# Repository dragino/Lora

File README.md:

Hardware and software source for Lora technology

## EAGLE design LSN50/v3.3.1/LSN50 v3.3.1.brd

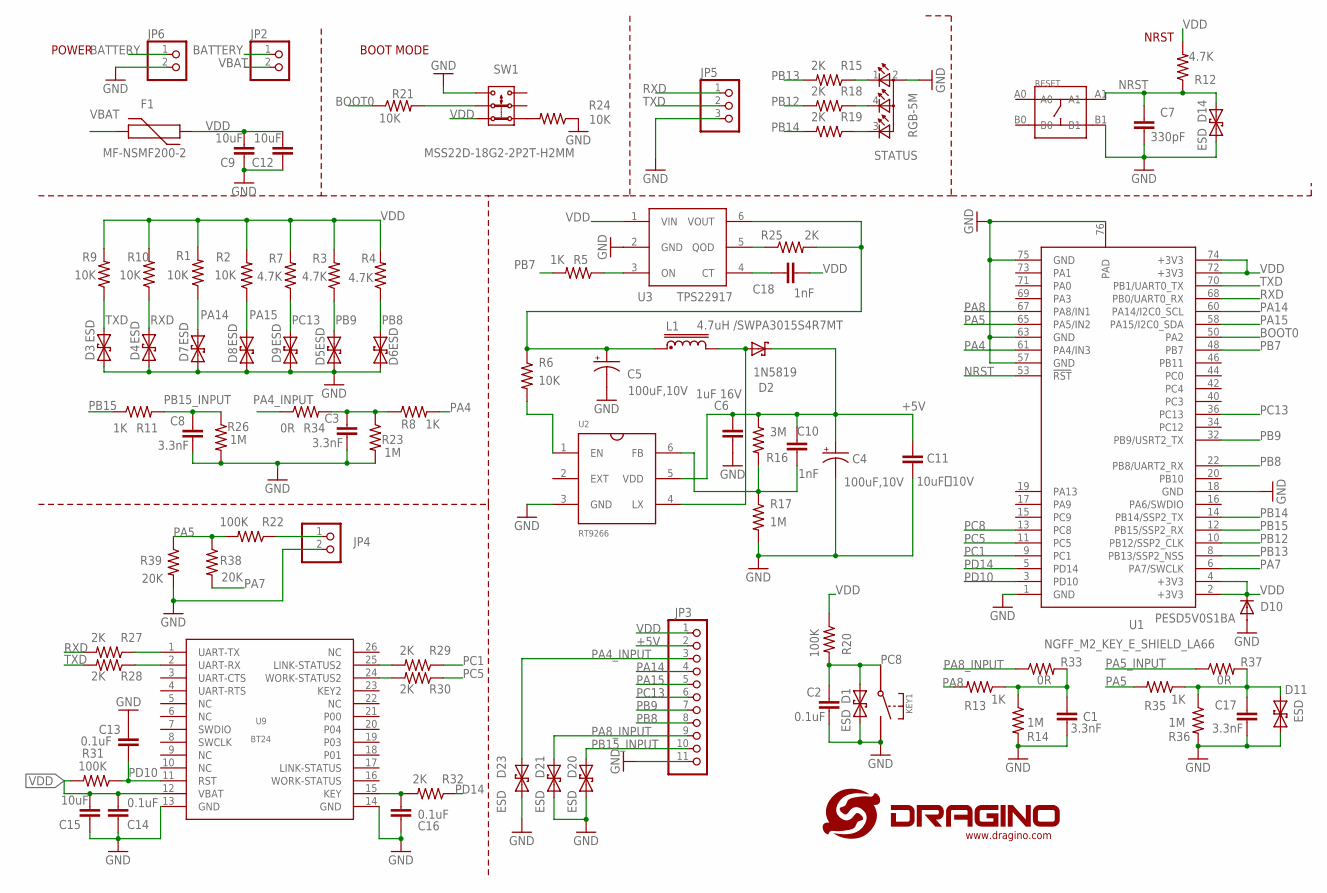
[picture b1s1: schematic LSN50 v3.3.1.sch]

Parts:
C1, C3, C8, C17: 3.3nF; C0402
C2, C13, C14, C16: 0.1uF; C0402
C4, C5: 100uF,10V; SMC_B
C6: 1uF 16V; C0603
C7: 330pF; C0402
C9, C12, C15: 10uF; C0805
C10, C18: 1nF; C0402
C11: 10uF，10V; C0805
D1, D3, D4, D5, D6, D7, D8, D9, D11, D14, D20, D21, D23: ESD; DFN1006
D2: 1N5819; SOD123FL
D10: PESD5V0S1BA; DIODE_SOD323-R
F1: MF-NSMF200-2; R1206
JP2: PINHD-1X2; 1X02
JP3: PINHD-1X11-MM; KF350-11P
JP4: PINHD-1X2-; PH2.0-2P
JP5: PINHD-1X3; 1X03
JP6: PINHD-1X2""; XH2.54-2P
KEY1: SWITCHDIL4; SWITCH_6X6X19_DIL4
L1: 4.7uH /SWPA3015S4R7MT; SWPA3010S
R1, R2, R6, R9, R10, R21, R24: 10K; R0402
R3, R4, R7, R12: 4.7K; R0402
R5, R8, R11, R13, R35: 1K; R0402
R14, R17, R23, R26, R36: 1M; R0603
R15, R18, R19, R25, R27, R28, R29, R30, R32: 2K; R0402
R16: 3M; R0402
R20, R22, R31: 100K; R0402
R33, R34, R37: 0R; R0603
R38, R39: 20K; R0402
RESET: 轻触开关3*3*1.5四脚贴片开关; SW4-SMD-3.35X3.35X1.5MM
STATUS: RGB-5M; RGB
SW1: MSS22D-18G2-2P2T-H2MM; MSS22D-18G2-2P2T-H2MM-DIL
U1: NGFF_M2_KEY_E_SHIELD_LA66; NGFF_M2_KEY_E_SHIELD
U2: RT9266; 6/SOT-23
U3: TPS22917; SOT23-6L
U9: BT24; BT24-SMD26

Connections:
+5V: C4.+, C6.2, C10.2, C11.2, D2.C, JP3.2, R16.1, U2.5 (VDD)
BATTERY: JP2.1, JP6.1
BOOT0: R21.1, U1.50 (PA2)
GND: C1.1, C2.1, C3.1, C4.-, C5.-, C6.1, C7.1, C8.1, C9.1, C11.1, C12.1, C13.2, C14.2, C15.1, C16.2, C17.1, D1.1, D3.1, D4.1, D5.1, D6.1, D7.1, D8.1, D9.1, D10.A, D11.1, D14.1, D20.1, D21.1, D23.1, JP3.11, JP4.2, JP5.3, JP6.2, KEY1.2, R14.2, R17.2, R23.2, R24.1, R26.2, R36.2, R39.2, RESET.B1, STATUS.2 (A), SW1.1, U1.1 (GND), U1.18 (GND), U1.57 (GND), U1.63 (GND), U1.75 (GND), U1.76 (PAD), U2.3 (GND), U3.2 (GND), U9.13 (GND), U9.14 (GND)
unnamed: R15.1, STATUS.1 (CRED)
unnamed: R24.2, SW1.4
unnamed: R5.1, U3.3 (ON)
unnamed: C10.1, R16.2, R17.1, U2.6 (FB)
unnamed: D2.A, L1.P$2 (4), U2.4 (LX)
unnamed: R18.1, STATUS.4 (CBLUE)
unnamed: R6.2, U2.1 (EN)
unnamed: R25.1, U3.5 (QOD)
unnamed: R19.1, STATUS.3 (CGREEN)
unnamed: C1.2, R13.1, R14.1, R33.2
unnamed: C5.+, L1.P$1 (1), R6.1, R25.2, U3.6 (VOUT)
unnamed: R27.1, U9.1 (UART-TX)
unnamed: R28.1, U9.2 (UART-RX)
unnamed: C16.1, R32.2, U9.15 (KEY)
unnamed: C3.2, R8.1, R23.1, R34.2
unnamed: R29.2, U9.25 (LINK-STATUS2)
unnamed: R30.2, U9.24 (WORK-STATUS2)
unnamed: C17.2, D11.2, R35.1, R36.1, R37.2
unnamed: R21.2, SW1.2
unnamed: C18.1, U3.4 (CT)
unnamed: JP4.1, R22.1
NRST: C7.2, D14.2, R12.1, RESET.A1, U1.53 (!RST)
PA4: R8.2, U1.61 (PA4/IN3)
PA4_INPUT: D23.2, JP3.3, R34.1
PA5: R22.2, R35.2, R38.1, R39.1, U1.65 (PA5/IN2)
PA5_INPUT: R37.1
PA7: R38.2, U1.6 (PA7/SWCLK)
PA8: R13.2, U1.67 (PA8/IN1)
PA8_INPUT: D21.2, JP3.9, R33.1
PA14: D7.2, JP3.4, R1.1, U1.60 (PA14/I2C0_SCL)
PA15: D8.2, JP3.5, R2.1, U1.58 (PA15/I2C0_SDA)
PB7: R5.2, U1.48 (PB7)
PB8: D6.2, JP3.8, R4.1, U1.22 (PB8/UART2_RX)
PB9: D5.2, JP3.7, R3.1, U1.32 (PB9/USRT2_TX)
PB12: R18.2, U1.10 (PB12/SSP2_CLK)
PB13: R15.2, U1.8 (PB13/SSP2_NSS)
PB14: R19.2, U1.14 (PB14/SSP2_TX)
PB15: R11.1, U1.12 (PB15/SSP2_RX)
PB15_INPUT: C8.2, D20.2, JP3.10, R11.2, R26.1
PC1: R29.1, U1.9 (PC1)
PC5: R30.1, U1.11 (PC5)
PC8: C2.2, D1.2, KEY1.1, R20.2, U1.13 (PC8)
PC13: D9.2, JP3.6, R7.1, U1.36 (PC13)
PD10: C13.1, R31.1, U1.3 (PD10), U9.11 (RST)
PD14: R32.1, U1.5 (PD14)
RXD: D4.2, JP5.1, R10.1, R27.2, U1.68 (PB0/UART0_RX)
TXD: D3.2, JP5.2, R9.1, R28.2, U1.70 (PB1/UART0_TX)
VBAT: F1.2, JP2.2
VDD: C9.2, C12.2, C14.1, C15.2, C18.2, D10.C, F1.1, JP3.1, R1.2, R2.2, R3.2, R4.2, R7.2, R9.2, R10.2, R12.2, R20.1, R31.2, SW1.3, U1.2 (+3V3), U1.4 (+3V3), U1.72 (+3V3), U1.74 (+3V3), U3.1 (VIN), U9.12 (VBAT)

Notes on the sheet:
BOOT MODE
NRST
POWER

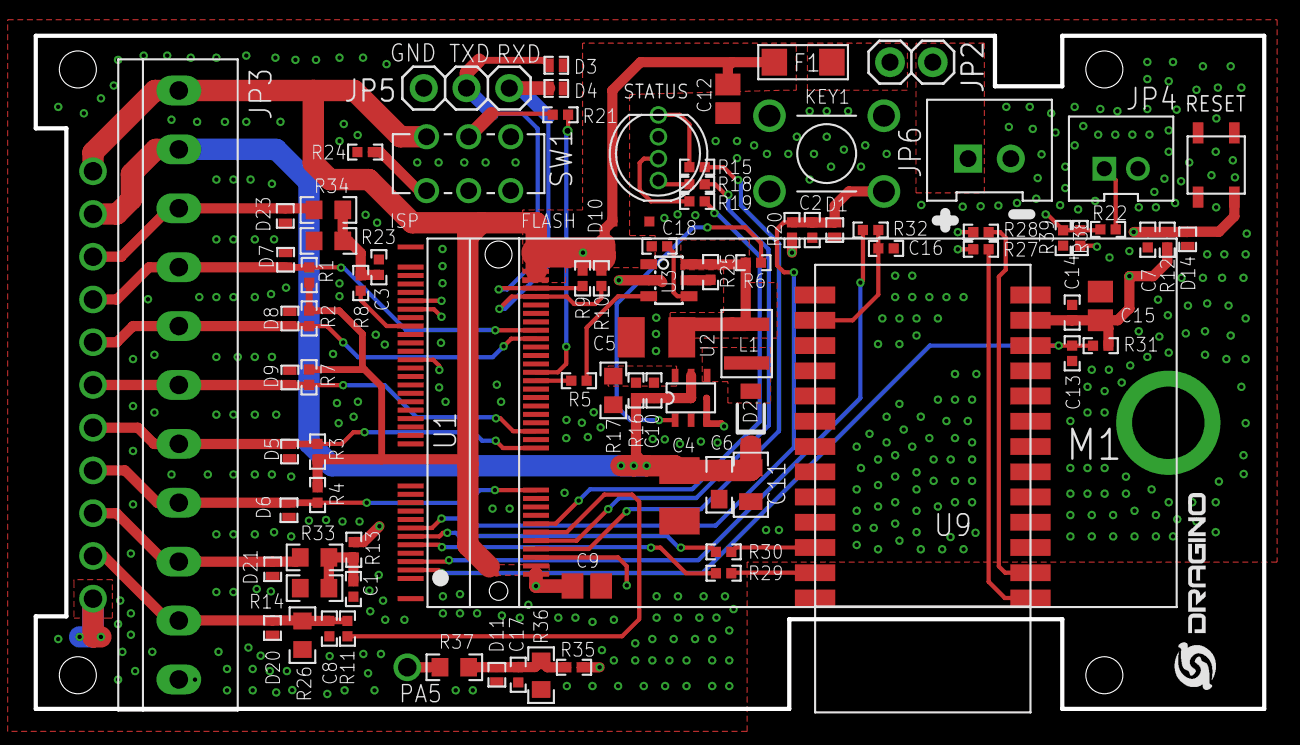
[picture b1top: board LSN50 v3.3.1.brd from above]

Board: 4 copper layers, 73.0 x 40.0 mm, 88 parts (0 on the bottom side), 52 nets.

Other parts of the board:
U$2: LOGO-NEW; LOGO-SILK-NEW

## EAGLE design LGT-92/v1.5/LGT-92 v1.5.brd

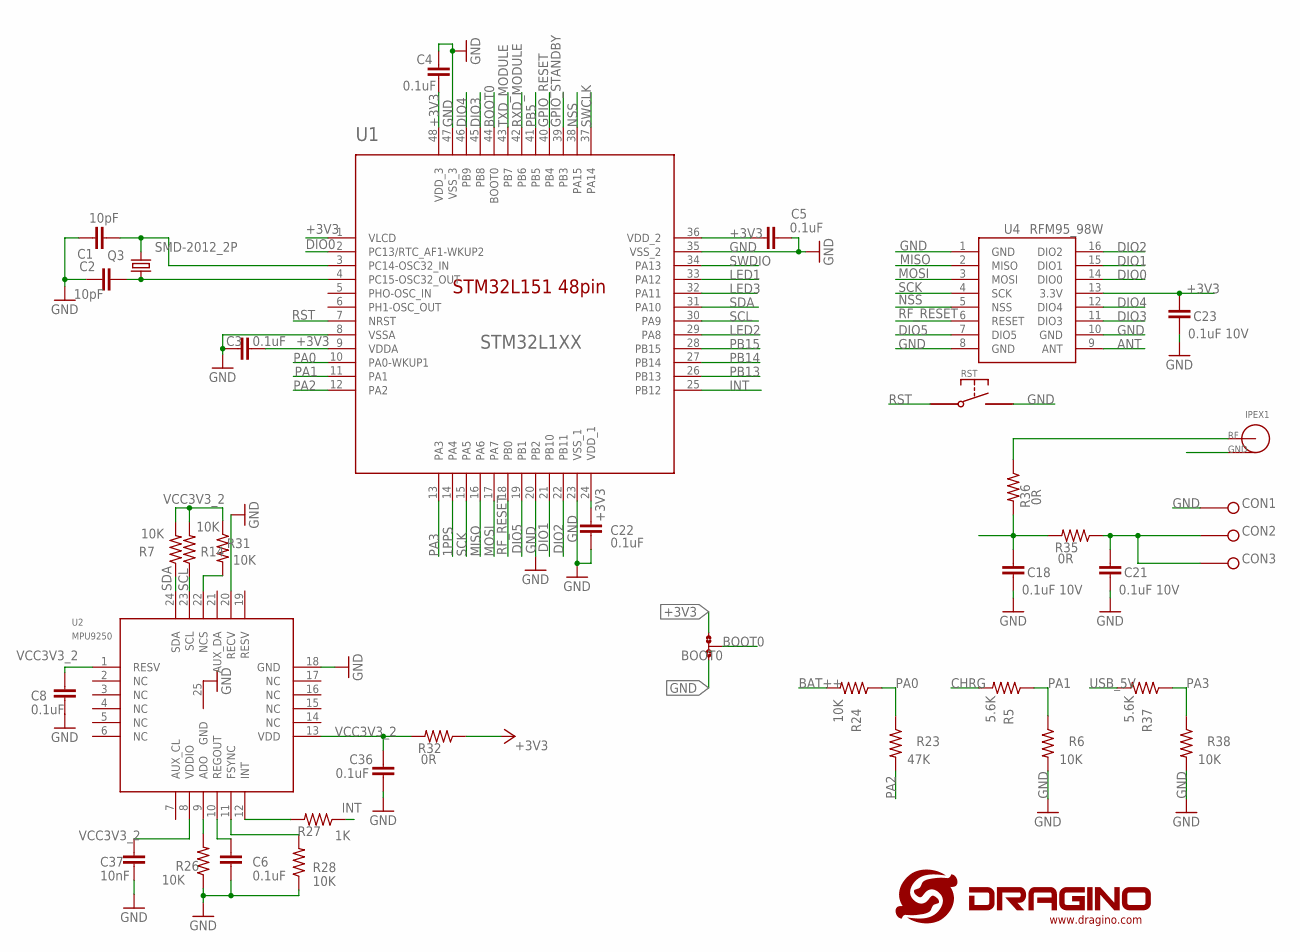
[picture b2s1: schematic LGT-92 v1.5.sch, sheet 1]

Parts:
BOOT0: 0R-JUMPA0R-JMP-0402; A0R-JMP-0402
C1, C2: 10pF; C0402
C3, C4, C5, C6, C8, C22, C36: 0.1uF; C0402
C18, C21, C23: 0.1uF 10V; C0402
C37: 10nF; C0402
CON1, CON2, CON3: POGOPINSMT-2.0; POGOPIN-SMT-2.0
IPEX1: I-PEX
Q3: SMD-2012_2P; 32.768K
R5, R37: 5.6K; R0402
R6, R7, R14, R24, R26, R28, R31, R38: 10K; R0402
R23: 47K; R0402
R27: 1K; R0402
R32, R35, R36: 0R; R0402
RST: SWITCHTS-017; TS-017
U1: STM32L1XX
U2: MPU9250; QFN-24
U4: RFM95_98W

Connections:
1: C21.2, CON2.1, CON3.1, R35.1
1PPS: U1.14 (PA4); also elsewhere on the board
+3V3: BOOT0.1, C3.1, C4.1, C5.2, C22.2, C23.2, R32.1, U1.1 (VLCD), U1.9 (VDDA), U1.24 (VDD_1), U1.36 (VDD_2), U1.48 (VDD_3), U4.13 (3.3V); also elsewhere on the board
ANT: C18.2, R35.2, R36.2, U4.9 (ANT)
BAT++: R24.2; also elsewhere on the board
BOOT0: BOOT0.2, U1.44 (BOOT0)
CHRG: R5.2; also elsewhere on the board
DIO0: U1.2 (PC13/RTC_AF1-WKUP2), U4.14 (DIO0)
DIO1: U1.21 (PB10), U4.15 (DIO1)
DIO2: U1.22 (PB11), U4.16 (DIO2)
DIO3: U1.45 (PB8), U4.11 (DIO3)
DIO4: U1.46 (PB9), U4.12 (DIO4)
DIO5: U1.19 (PB1), U4.7 (DIO5)
GND: BOOT0.3, C1.1, C2.1, C3.2, C4.2, C5.1, C6.1, C8.1, C18.1, C21.1, C22.1, C23.1, C36.1, C37.1, CON1.1, IPEX1.GND, IPEX1.GND1 (GND), R6.2, R26.1, R28.1, R38.2, RST.P$2, U1.8 (VSSA), U1.20 (PB2), U1.23 (VSS_1), U1.35 (VSS_2), U1.47 (VSS_3), U2.18 (GND), U2.20 (RECV), U2.25 (GND), U4.1 (GND), U4.8 (GND), U4.10 (GND); also elsewhere on the board
GPIO_RESET: U1.40 (PB4); also elsewhere on the board
GPIO_STANDBY: U1.39 (PB3); also elsewhere on the board
INT: R27.1, U1.25 (PB12)
LED1: U1.33 (PA12); also elsewhere on the board
LED2: U1.29 (PA8); also elsewhere on the board
LED3: U1.32 (PA11); also elsewhere on the board
MISO: U1.16 (PA6), U4.2 (MISO)
MOSI: U1.17 (PA7), U4.3 (MOSI)
unnamed: C2.2, Q3.3 (1), U1.4 (PC15-OSC32_OUT)
unnamed: C1.2, Q3.4 (2), U1.3 (PC14-OSC32_IN)
unnamed: R31.2, U2.22 (NCS)
unnamed: IPEX1.SIG, R36.1
unnamed: R26.2, U2.9 (ADO)
unnamed: C6.2, U2.10 (REGOUT)
unnamed: R28.2, U2.11 (FSYNC)
unnamed: R27.2, U2.12 (INT)
NSS: U1.38 (PA15), U4.5 (NSS)
PA0: R23.1, R24.1, U1.10 (PA0-WKUP1)
PA1: R5.1, R6.1, U1.11 (PA1)
PA2: R23.2, U1.12 (PA2)
PA3: R37.1, R38.1, U1.13 (PA3)
PB5: U1.41 (PB5); also elsewhere on the board
PB13: U1.26 (PB13)
PB14: U1.27 (PB14); also elsewhere on the board
PB15: U1.28 (PB15)
RF_RESET: U1.18 (PB0), U4.6 (RESET)
RST: RST.P$1, U1.7 (NRST)
RXD_MODULE: U1.42 (PB6); also elsewhere on the board
SCK: U1.15 (PA5), U4.4 (SCK)
SCL: R14.1, U1.30 (PA9), U2.23 (SCL)
SDA: R7.1, U1.31 (PA10), U2.24 (SDA)
SWCLK: U1.37 (PA14); also elsewhere on the board
SWDIO: U1.34 (PA13); also elsewhere on the board
TXD_MODULE: U1.43 (PB7); also elsewhere on the board
USB_5V: R37.2; also elsewhere on the board
VCC3V3_2: C8.2, C36.2, C37.2, R7.2, R14.2, R31.1, R32.2, U2.1 (RESV), U2.8 (VDDIO), U2.13 (VDD)

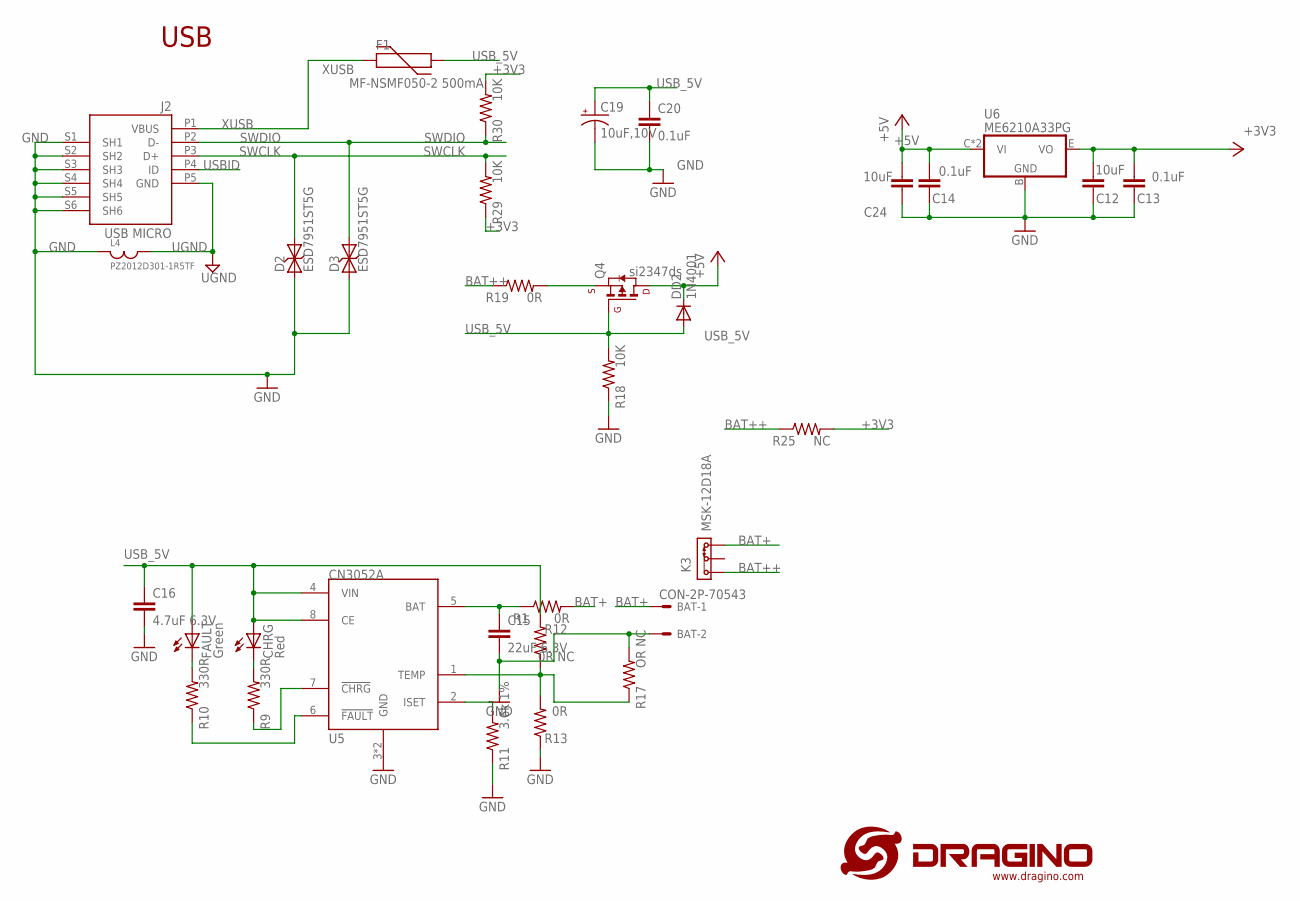
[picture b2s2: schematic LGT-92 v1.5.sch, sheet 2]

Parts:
BAT: CON-2P-70543; 70543-02
C12, C24: 10uF; C0805
C13, C14, C20: 0.1uF; C0402
C15: 22uF 6.3V; C0603
C16: 4.7uF 6.3V; C0603
C19: 10uF,10V; SMC_A
CHRG: Red; DRAGINO_CHIPLED_0603
D2, D3: ESD7951ST5G; SOD?923
DD2: 1N4001; DIODE_DO214AC
F1: MF-NSMF050-2 500mA; R1206$1
FAULT: Green; DRAGINO_CHIPLED_0603
J2: USB MICRO; CON2_USB_MICRO_B_AT
K3: MSK-12D18A
L4: PZ2012D301-1R5TF; C0805
Q4: si2347ds; SOT-23-HIGH-POWER
R1, R19: 0R; R0805
R9, R10: 330R; R0402
R11: 3.6k 1%; R0402
R12: 0R NC; R0402
R13: 0R; R0402
R17: OR NC; R0402
R18, R29, R30: 10K; R0402
R25: NC; R0805
U5: CN3052A
U6: ME6210A33PG; SOT-89

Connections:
+3V3: C12.2, C13.2, R25.2, R29.1, R30.2, U6.E (VO); also elsewhere on the board
+5V: C14.2, C24.2, DD2.C, Q4.1 (D), U6.C (VI), U6.C@1 (VI)
BAT+: BAT.1 (S), K3.3, R1.2
BAT++: K3.1, R19.1, R25.1; also elsewhere on the board
CHRG: R9.1, U5.7 (!CHRG); also elsewhere on the board
GND: BAT.2, C12.1, C13.1, C14.1, C15.2, C16.2, C19.-, C20.2, C24.1, D2.P$1 (1), D3.P$1 (1), J2.S1 (SH1), J2.S2 (SH2), J2.S3 (SH3), J2.S4 (SH4), J2.S5 (SH5), J2.S6 (SH6), L4.1, R11.1, R13.1, R17.2, R18.1, U5.3 (GND), U5.P$1 (GND), U6.B (GND); also elsewhere on the board
unnamed: C15.1, R1.1, U5.5 (BAT)
unnamed: CHRG.C, R9.2
unnamed: FAULT.C, R10.2
unnamed: Q4.2 (S), R19.2
unnamed: R10.1, U5.6 (!FAULT)
unnamed: R12.1, R13.2, R17.1, U5.1 (TEMP)
unnamed: R11.2, U5.2 (ISET)
SWCLK: D2.P$2 (2), J2.P3 (D+), R29.2; also elsewhere on the board
SWDIO: D3.P$2 (2), J2.P2 (D-), R30.1; also elsewhere on the board
UGND: J2.P5 (GND), L4.2
USBID: J2.P4 (ID)
USB_5V: C16.1, C19.+, C20.1, CHRG.A, DD2.A, F1.1, FAULT.A, Q4.3 (G), R12.2, R18.2, U5.4 (VIN), U5.8 (CE); also elsewhere on the board
XUSB: F1.2, J2.P1 (VBUS)

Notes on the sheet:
USB

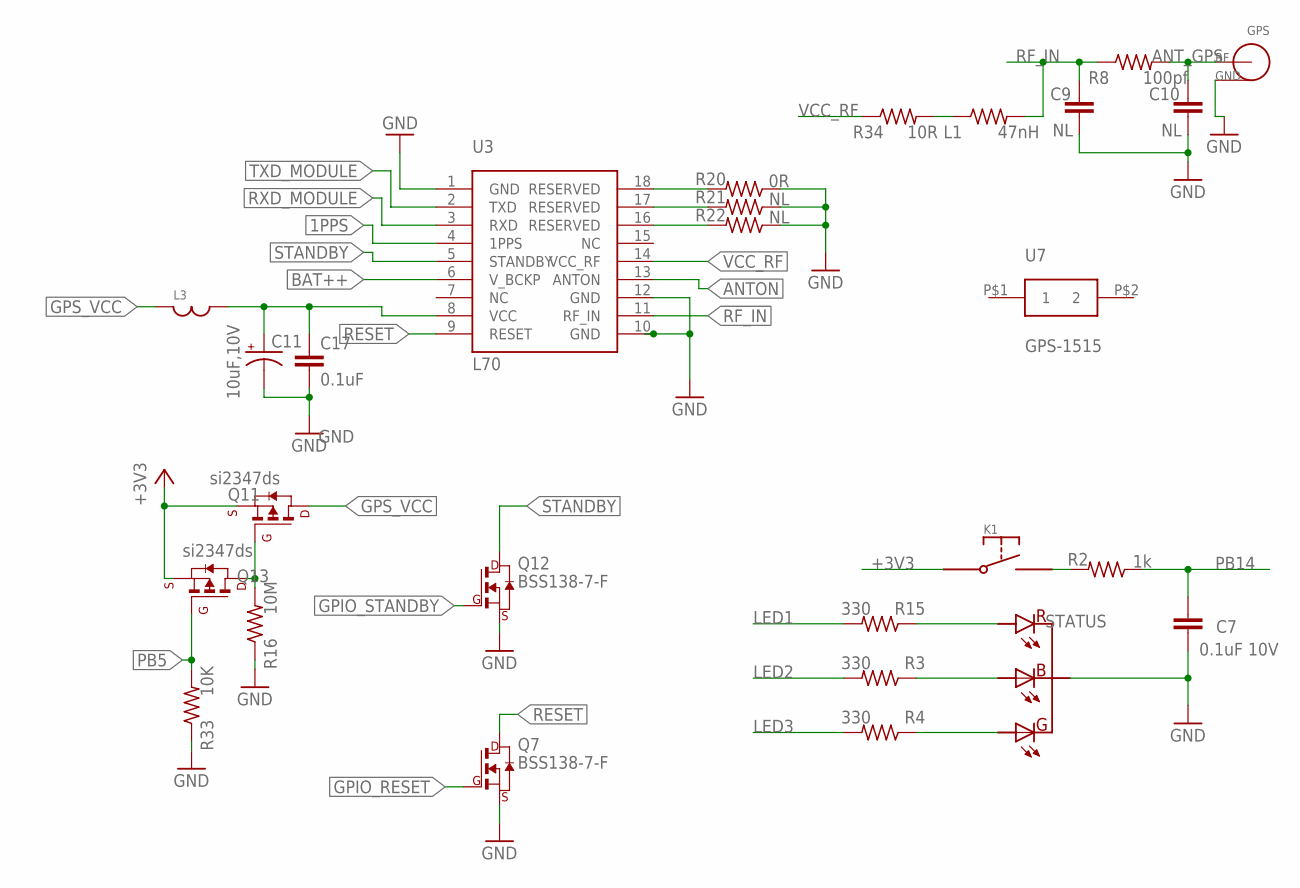
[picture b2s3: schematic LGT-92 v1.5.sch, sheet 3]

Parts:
C7: 0.1uF 10V; C0402
C9, C10: NL; C0402
C11: 10uF,10V; SMC_A
C17: 0.1uF; C0402
GPS: I-PEX,NL; I-PEX
K1: S-LAY; KEY
L1: 47nH; R0402
L3: JLC-PZ2012D800-3R0TF; C0805
Q7, Q12: BSS138-7-F; SOT-23
Q11, Q13: si2347ds; SOT-23-HIGH-POWER
R2: 1k; R0402
R3, R4, R15: 330; R0402
R8: 100pf; R0402
R16: 10M; R0402
R20: 0R; R0402
R21, R22: NL; R0402
R33: 10K; R0402
R34: 10R; R0402
STATUS: LED-RGB-THR-5MM-GNDSMD-3528; LED-3528
U3: L70
U7: GPS-1515; GPS-YY

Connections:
1PPS: U3.4 (1PPS); also elsewhere on the board
+3V3: K1.1, K1.2, K1.5, Q11.2 (S), Q13.2 (S); also elsewhere on the board
ANTON: U3.13 (ANTON)
ANT_GPS: C10.1, GPS.SIG, R8.2
BAT++: U3.6 (V_BCKP); also elsewhere on the board
GND: C7.1, C9.2, C10.2, C11.-, C17.2, GPS.GND, GPS.GND1 (GND), Q7.2 (S), Q12.2 (S), R16.1, R20.1, R21.1, R22.1, R33.1, STATUS.+ (C), U3.1 (GND), U3.10 (GND), U3.12 (GND); also elsewhere on the board
GPIO_RESET: Q7.3 (G); also elsewhere on the board
GPIO_STANDBY: Q12.3 (G); also elsewhere on the board
GPS_VCC: L3.1, Q11.1 (D)
GPS_VCC1: C11.+, C17.1, L3.2, U3.8 (VCC)
LED1: R15.2; also elsewhere on the board
LED2: R3.2; also elsewhere on the board
LED3: R4.2; also elsewhere on the board
unnamed: L1.1, R34.2
unnamed: R15.1, STATUS.R- (1)
unnamed: Q11.3 (G), Q13.1 (D), R16.2
unnamed: K1.3, K1.4, K1.6, R2.2
unnamed: R3.1, STATUS.B- (3)
unnamed: R4.1, STATUS.G- (4)
unnamed: R20.2, U3.18 (RESERVED)
unnamed: R21.2, U3.17 (RESERVED)
unnamed: R22.2, U3.16 (RESERVED)
PB5: Q13.3 (G), R33.2; also elsewhere on the board
PB14: C7.2, R2.1; also elsewhere on the board
RESET: Q7.1 (D), U3.9 (RESET)
RF_IN: C9.1, L1.2, R8.1, U3.11 (RF_IN)
RXD_MODULE: U3.3 (RXD); also elsewhere on the board
STANDBY: Q12.1 (D), U3.5 (STANDBY)
TXD_MODULE: U3.2 (TXD); also elsewhere on the board
VCC_RF: R34.1, U3.14 (VCC_RF)

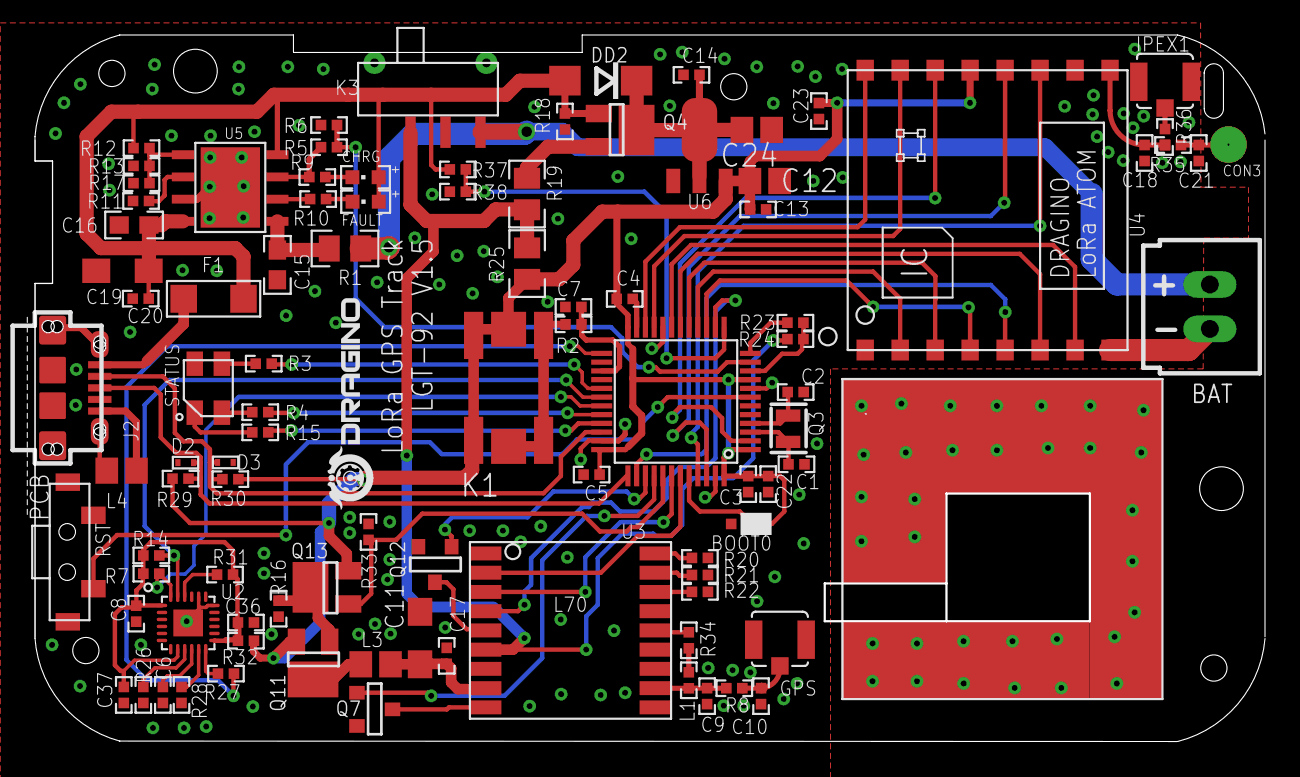
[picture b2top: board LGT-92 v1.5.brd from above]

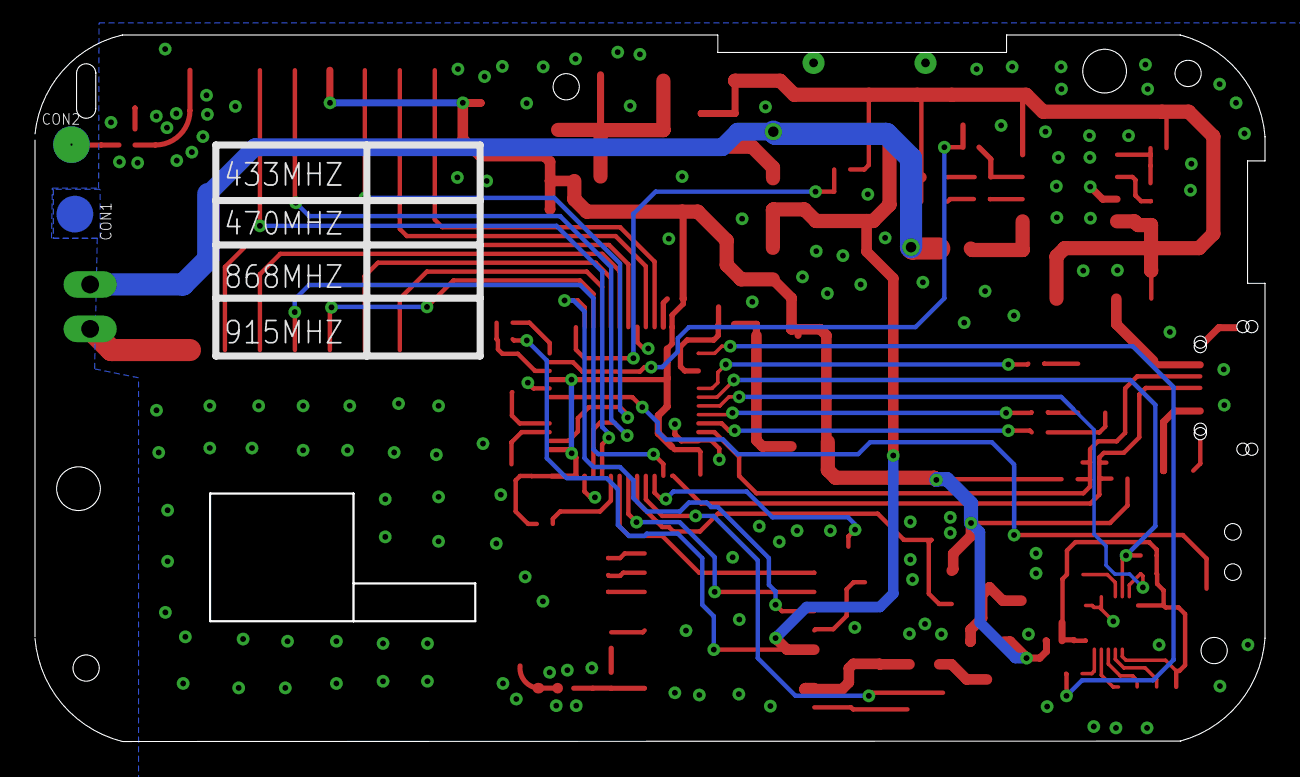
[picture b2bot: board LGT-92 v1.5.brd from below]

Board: 4 copper layers, 70.2 x 40.3 mm, 99 parts (2 on the bottom side), 75 nets.

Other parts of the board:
U$1: LOGO-DRAGINO-2018

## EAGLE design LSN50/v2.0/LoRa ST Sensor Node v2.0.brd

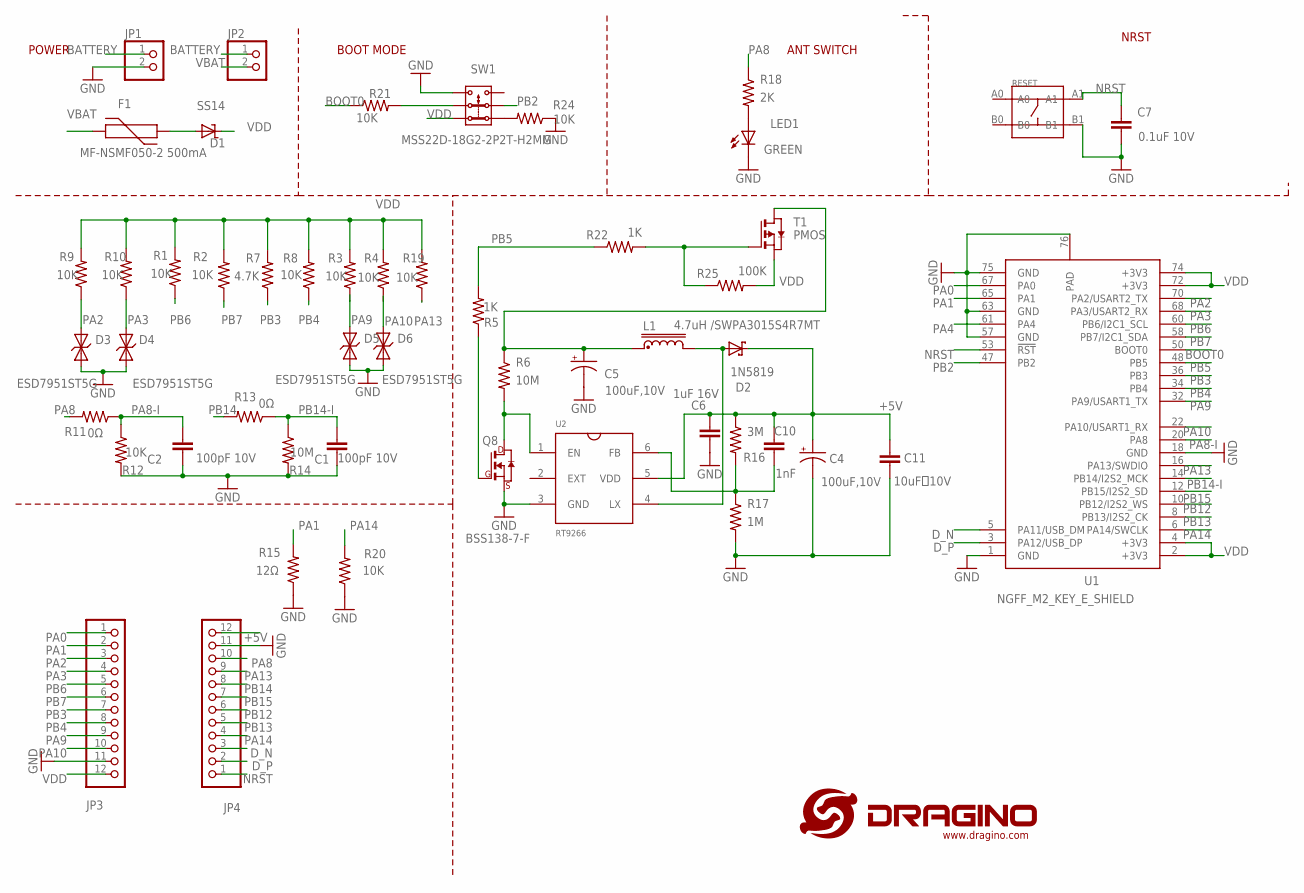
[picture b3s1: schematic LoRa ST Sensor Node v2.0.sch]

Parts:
C1, C2: 100pF 10V; C0603
C4, C5: 100uF,10V; SMC_B
C6: 1uF 16V; C0603
C7: 0.1uF 10V; C0402
C10: 1nF; C0402
C11: 10uF，10V; C0805
D1: SS14; DO214AC
D2: 1N5819; SOD123FL
D3, D4, D5, D6: ESD7951ST5G; SOD−923
F1: MF-NSMF050-2 500mA; R1206
JP1: PINHD-1X2L; XH2.54-2P-L
JP2: PINHD-1X2; 1X02
JP3, JP4: PINHD-1X12""; 1X12-DIP
L1: 4.7uH /SWPA3015S4R7MT; SWPA3010S
LED1: GREEN; CHIPLED_0603
Q8: BSS138-7-F; SOT-23
R1, R2, R3, R4, R8, R9, R10, R19, R20, R21, R24: 10K; R0402
R5, R22: 1K; R0402
R6: 10M; R0402
R7: 4.7K; R0402
R11, R13: 0Ω; R0603
R12: 10K; R0603
R14: 10M; R0603
R15: 12Ω; R1206@1
R16: 3M; R0402
R17: 1M; R0402
R18: 2K; R0402
R25: 100K; R0402
RESET: 轻触开关3*3*1.5四脚贴片开关; SW4-SMD-3.35X3.35X1.5MM
SW1: MSS22D-18G2-2P2T-H2MM; MSS22D-18G2-2P2T-H2MM-DIL
T1: PMOS; SOT-23
U1: NGFF_M2_KEY_E_SHIELD
U2: RT9266; 6/SOT-23

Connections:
+5V: C4.+, C6.2, C10.2, C11.2, D2.C, JP4.12, R16.1, U2.5 (VDD)
BATTERY: JP1.1, JP2.1
BOOT0: R21.1, U1.50 (BOOT0)
D_N: JP4.3, U1.5 (PA11/USB_DM)
D_P: JP4.2, U1.3 (PA12/USB_DP)
GND: C1.1, C2.1, C4.-, C5.-, C6.1, C7.1, C11.1, D3.P$2 (2), D4.P$2 (2), D5.P$2 (2), D6.P$2 (2), JP1.2, JP3.11, JP4.11, LED1.C, Q8.2 (S), R12.2, R14.2, R15.1, R17.2, R20.1, R24.1, RESET.B1, SW1.1, U1.1 (GND), U1.18 (GND), U1.57 (GND), U1.63 (GND), U1.75 (GND), U1.76 (PAD), U2.3 (GND)
unnamed: LED1.A, R18.2
unnamed: R24.2, SW1.4
unnamed: Q8.3 (G), R5.1
unnamed: C10.1, R16.2, R17.1, U2.6 (FB)
unnamed: D2.A, L1.P$2 (4), U2.4 (LX)
unnamed: Q8.1 (D), R6.2, U2.1 (EN)
unnamed: R22.2, R25.1, T1.3 (G)
unnamed: D1.A, F1.1
unnamed: C5.+, L1.P$1 (1), R6.1, T1.1 (D)
unnamed: R21.2, SW1.2
NRST: C7.2, JP4.1, RESET.A1, U1.53 (!RST)
PA0: JP3.1, U1.67 (PA0)
PA1: JP3.2, R15.2, U1.65 (PA1)
PA2: D3.P$1 (1), JP3.3, R9.1, U1.70 (PA2/USART2_TX)
PA3: D4.P$1 (1), JP3.4, R10.1, U1.68 (PA3/USART2_RX)
PA4: U1.61 (PA4)
PA8: JP4.10, R11.2, R18.1
PA8-I: C2.2, R11.1, R12.1, U1.20 (PA8)
PA9: D5.P$1 (1), JP3.9, R3.1, U1.32 (PA9/USART1_TX)
PA10: D6.P$1 (1), JP3.10, R4.1, U1.22 (PA10/USART1_RX)
PA13: JP4.9, R19.1, U1.16 (PA13/SWDIO)
PA14: JP4.4, R20.2, U1.6 (PA14/SWCLK)
PB2: SW1.5, U1.47 (PB2)
PB3: JP3.7, R7.1, U1.36 (PB3)
PB4: JP3.8, R8.1, U1.34 (PB4)
PB5: R5.2, R22.1, U1.48 (PB5)
PB6: JP3.5, R1.1, U1.60 (PB6/I2C1_SCL)
PB7: JP3.6, R2.1, U1.58 (PB7/I2C1_SDA)
PB12: JP4.6, U1.10 (PB12/I2S2_WS)
PB13: JP4.5, U1.8 (PB13/I2S2_CK)
PB14: JP4.8, R13.2
PB14-I: C1.2, R13.1, R14.1, U1.14 (PB14/I2S2_MCK)
PB15: JP4.7, U1.12 (PB15/I2S2_SD)
VBAT: F1.2, JP2.2
VDD: D1.C, JP3.12, R1.2, R2.2, R3.2, R4.2, R7.2, R8.2, R9.2, R10.2, R19.2, R25.2, SW1.3, T1.2 (S), U1.2 (+3V3), U1.4 (+3V3), U1.72 (+3V3), U1.74 (+3V3)

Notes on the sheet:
BOOT MODE
NRST
POWER
ANT SWITCH

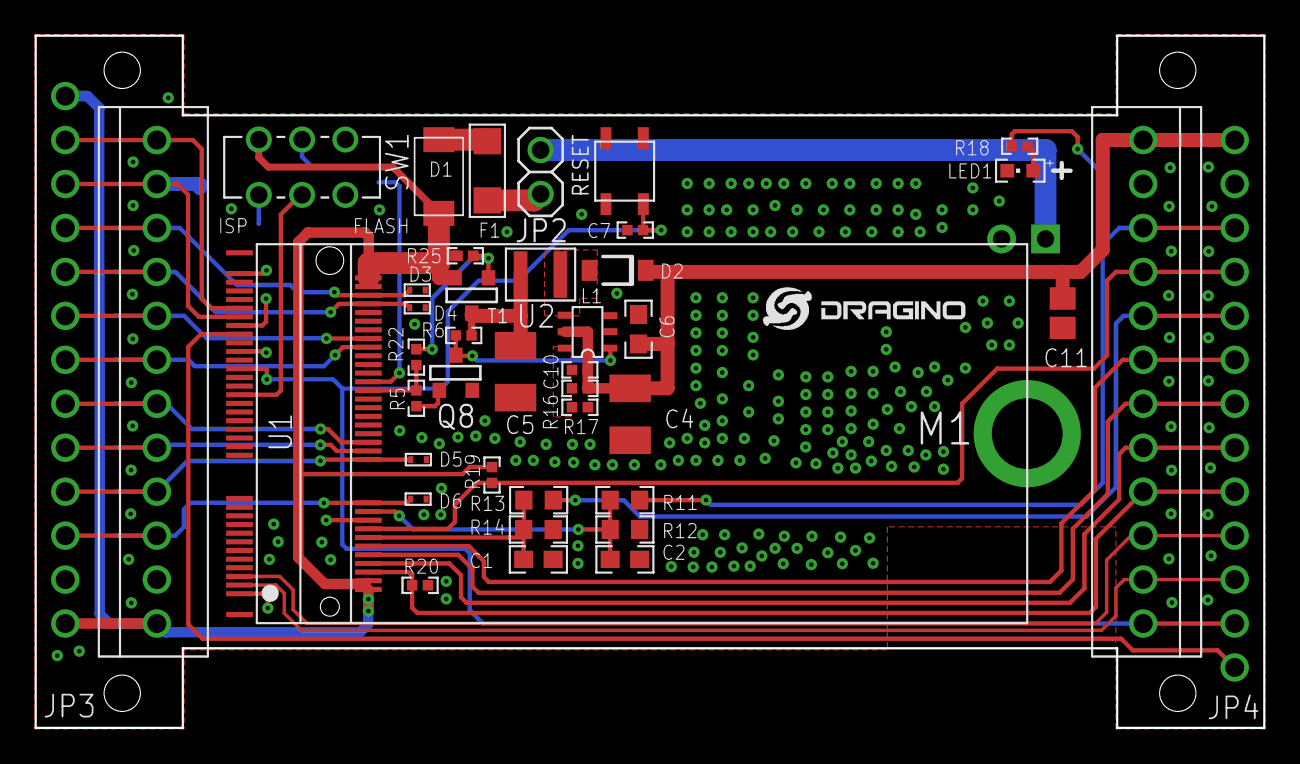
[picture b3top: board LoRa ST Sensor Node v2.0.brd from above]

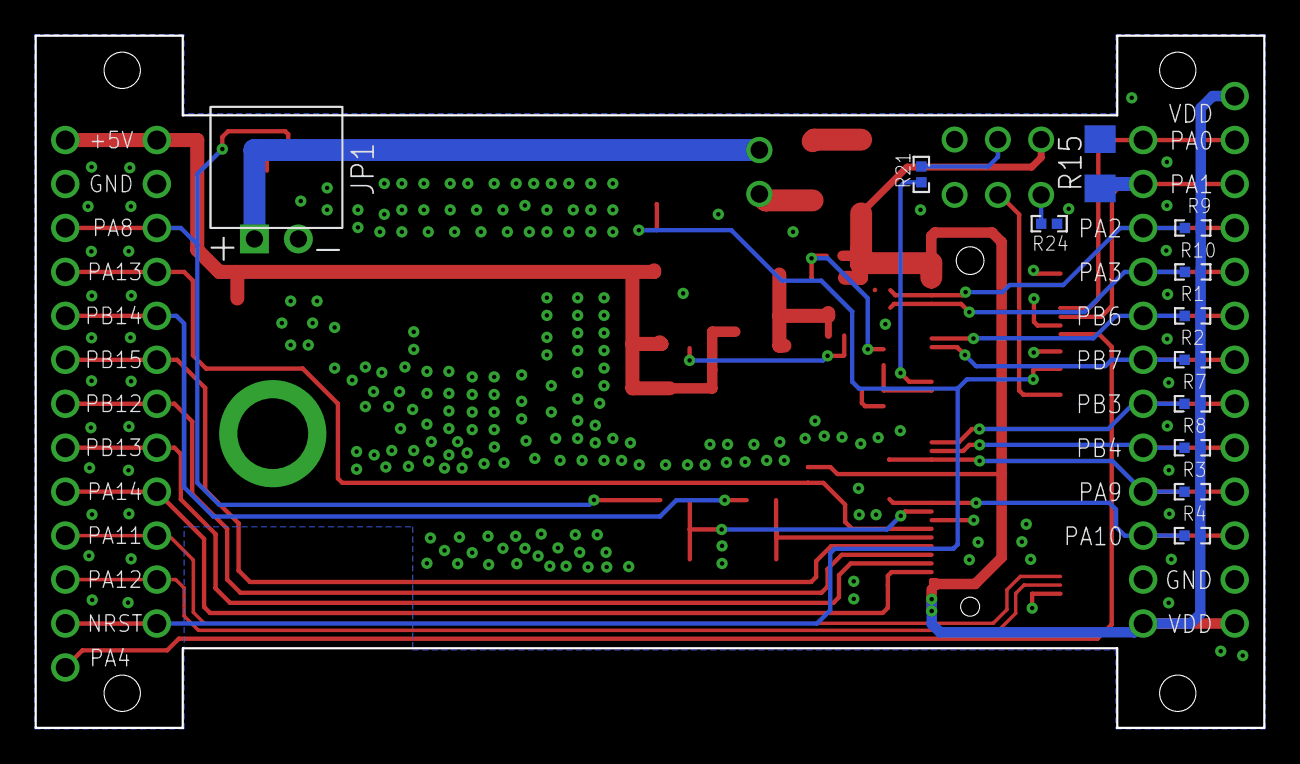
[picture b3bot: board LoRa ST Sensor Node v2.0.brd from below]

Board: 2 copper layers, 71.0 x 40.0 mm, 53 parts (12 on the bottom side), 40 nets.

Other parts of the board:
U$1: LORA_ST_SENSOR_NODE_V2
U$2: LOGO-NEW; LOGO-SILK-NEW

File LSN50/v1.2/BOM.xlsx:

产品型号: LoRa ST Sensor Node v1.2
序号 | Part | Value | Device | MF | MPN | 用量 | 生产数量 | 生产需求 | 库存 | 单价 | 价格 | 备注
1 | D1 | M7 | DO214AC |  |  | 1
2 | D2 | 1N5819HW-7-F | SOD-123 |  |  | 1 |  |  |  |  |  | https://item.szlcsc.com/83701.html
3 | C4,C5 | 100uF,10V | CASE-B_3528 |  |  | 2 |  |  |  |  |  | https://item.szlcsc.com/112007.html
4 | C6 | 1uF,16V | C-EUC0603 |  |  | 1 |  |  |  |  |  | https://item.szlcsc.com/1944.html
5 | C7 | 0.1uF,10V | C-EUC0402 |  |  | 1
6 | C10 | 1nF | C-EUC0402 |  |  | 1
7 | C11 | 10uF，10V | C-EUC0805 |  |  | 1
8 | JP3,JP4 | PINHD-1X12 | 1X12-DIP |  |  | 2 |  | 2.54-12P |  |  |  | https://item.taobao.com/item.htm?spm=a230r.1.14.61.704ff023s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
9 | L1 | 4.7uH /SWPA3015S4R7MT | 3015 |  |  | 1 |  |  |  |  |  | https://so.szlcsc.com/global.html?c=&k=SWPA3015S4R7MT
10 | LED1 | LEDCHIP-LED0603 | LED0603 |  |  | 1 |  | 绿光
11 | JP1 | PINHD-1X2POWER | 1X02-DIP |  |  | 1 |  | 弯针插座 |  |  |  | https://item.taobao.com/item.htm?id=536135112476&ali_refid=a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
12 | JP2 | PINHD-1X02 | 1X02-2.54mm |  |  | 1 |  | 排针
13 | R1,R2,R3,R4,R9,R10,R21,R24 | 10K,0402 | R-US-R0402 |  |  | 8
14 | R11,R13 | 0Ω,0603 | R-US-R0603 |  |  | 2
15 | R7 | 4.7K,0402 | R-US-R0402 |  |  | 1
16 | R5 | 1K,0402 | R-US-R0402 |  |  | 1
17 | R6 | 9.1M,0402 | R-US-R0402 |  |  | 1
18 | R16 | 3M,0402 | R-US_R0402 |  |  | 1
19 | R17 | 1M,0402 | R-US_R0402 |  |  | 1
20 | R18 | 2K,0402 | R-US_R0402 |  |  | 1
21 | Q8 | BSS138-7-F NMOSFET | SOT-23 |  |  | 1
22 | RESET | 轻触开关3*3*1.5四脚贴片开关 | SW4-SMD |  |  | 1
23 | SW1 | MSS22D-18G2-2P2T-H2MM | 2P2T |  |  | 1
24 | U1 | NGFF_M2_KEY_E_SHIELD | NGFF_M2_KEY_E_SHIELD |  |  | 1 |  | E-Key 11+12 4.2 |  |  |  | https://item.taobao.com/item.htm?id=547604890617&ali_refid=a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
25 | U2 | RT9266GE | 6/SOT-23 |  |  | 1 |  |  |  |  |  | https://item.szlcsc.com/19278.html
26 | C1,C2（空贴） | 100pF,10V,0603 | C-EUC0603 |  |  | 2
27 | R8,R12,R14,R19,R20,R23（空贴） | 10K,0402 | R-US-R0402 |  |  | 6
28 | R15(空贴) | 12Ω,1206 | R-US_R1206 |  |  | 1
 | M2*20+3mm单头铜柱 |  |  |  |  | 3
 | M2螺母 |  |  |  |  | 3
 | M2*5螺钉 |  |  |  |  | 3
 | M3*5.56 |  |  |  |  | 1
 | M3*5螺钉 |  |  |  |  | 1
 | M4*8螺钉 |  |  |  |  | 2
 | 如需接中断传感器（如金属探测、光电、磁性）请将R11,R13贴20k,0603,R14,R12贴上,C1,C2也贴上

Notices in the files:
parts and their libraries:
dragino: http://creativecommons.org/licenses/by-sa/3.0
dragino: Released under the CC Attribution Share-Alike 3.0 License
